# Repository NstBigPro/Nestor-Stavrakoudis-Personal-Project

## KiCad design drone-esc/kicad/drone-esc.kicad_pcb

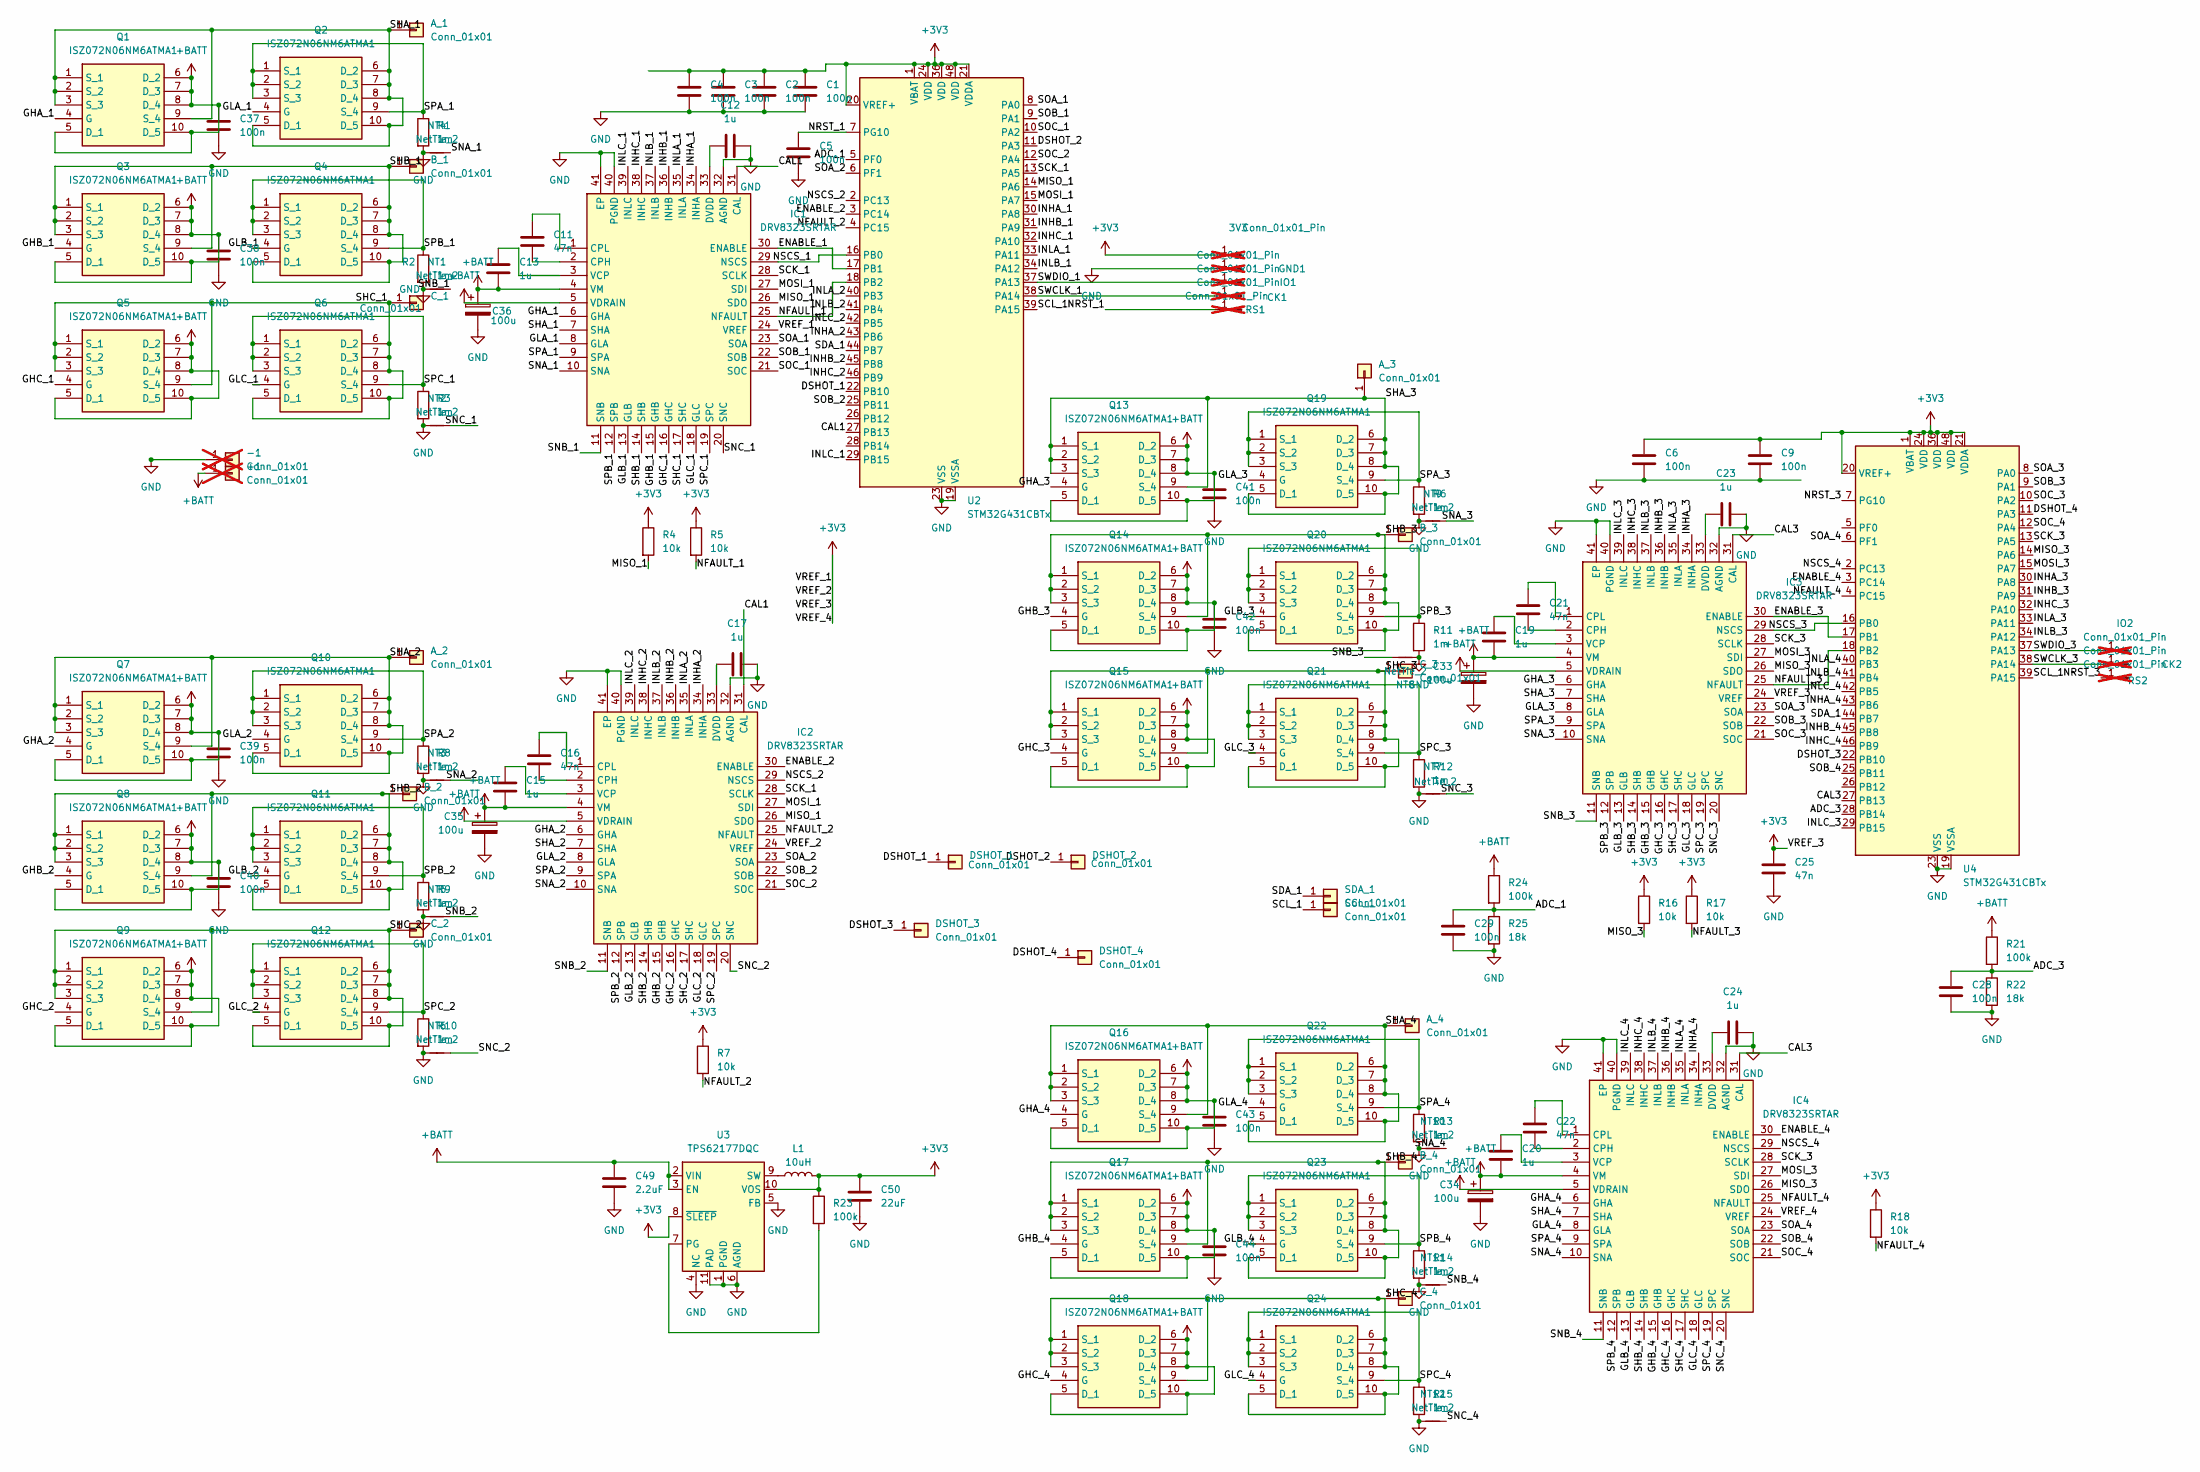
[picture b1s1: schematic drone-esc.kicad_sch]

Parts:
3V3: Conn_01x01_Pin; TestPoint_Pad_D1.0mm; not fitted
+1: Conn_01x01; TestPoint_Loop_D3.80mm_Drill2.5mm; not fitted
-1: Conn_01x01; TestPoint_Loop_D3.80mm_Drill2.5mm; not fitted
A_1, A_2, A_3, A_4: Conn_01x01; SolderWirePad_1x01_SMD_3x6mm
B_1, B_2, B_3, B_4: Conn_01x01; SolderWirePad_1x01_SMD_3x6mm
C1, C2, C3, C4, C5, C6, C9, C28, C29: 100n; C_0402_1005Metric; Mouser Part Number 80-C0402C104K8R7411
C11, C16, C21, C22, C25: 47n; C_0402_1005Metric; Mouser Part Number 81-GRM155R71H473KE4D
C12, C13, C15, C17, C19, C20, C23, C24: 1u; C_0402_1005Metric; Mouser Part Number 346-CM05X5R105M35AH
C33, C34, C35, C36: 100u; CP_Radial_D8.0mm_P3.50mm; Mouser Part Number 667-EEH-AZC1V101B
C37, C38, C39, C40, C41, C42, C43, C44: 100n; C_0805_2012Metric; Mouser Part Number 963-MCASG21GSB5104KT
C49: 2.2uF; C_0805_2012Metric; Mouser Part Number 81-GCJ21BD7YA225KE2L
C50: 22uF; C_0805_2012Metric; Mouser Part Number 963-MLASL21GBB5226MT
CK1, CK2: Conn_01x01_Pin; TestPoint_Pad_D1.0mm; not fitted
C_1, C_2, C_3, C_4: Conn_01x01; SolderWirePad_1x01_SMD_3x6mm
DSHOT_1, DSHOT_2, DSHOT_3, DSHOT_4: Conn_01x01; SolderWirePad_1x01_SMD_3x6mm
GND1: Conn_01x01_Pin; TestPoint_Pad_D1.0mm; not fitted
IC1, IC2, IC3, IC4: DRV8323SRTAR; DRV8323; Manufacturer_Part_Number DRV8323SRTAR; Mouser Part Number 595-DRV8323SRTAT
IO1, IO2: Conn_01x01_Pin; TestPoint_Pad_D1.0mm; not fitted
L1: 10uH; VLS3015; Mouser Part Number 810-VLS3015CX-100M-1
NT1, NT2, NT3, NT4, NT5, NT6, NT7, NT8, NT9, NT10, NT11, NT12: NetTie_2; NetTie-2_SMD_Pad0.5mm
Q1, Q2, Q3, Q4, Q5, Q6, Q7, Q8, Q9, Q10, Q11, Q12, Q13, Q14, Q15, Q16, Q17, Q18, Q19, Q20, Q21, Q22, Q23, Q24: ISZ072N06NM6ATMA1; Manufacturer_Part_Number ISZ072N06NM6ATMA1; Mouser Part Number 726-ISZ072N06NM6ATMA
R1, R2, R3, R6, R8, R9, R10, R11, R12, R13, R14, R15: 1m; R_2512_6332Metric; Mouser Part Number 755-PMR100HZP7FV1L00
R4, R5, R7, R16, R17, R18: 10k; R_0402_1005Metric; Mouser Part Number 603-RT0402FRE0710KL
R21, R23, R24: 100k; R_0402_1005Metric; Mouser Part Number 603-RT0402BRE07100KL
R22, R25: 18k; R_0402_1005Metric; Mouser Part Number 603-AC0402JR-0718KL
RS1, RS2: Conn_01x01_Pin; TestPoint_Pad_D1.0mm; not fitted
SCL_1: Conn_01x01; SolderWirePad_1x01_SMD_2x4mm
SDA_1: Conn_01x01; SolderWirePad_1x01_SMD_2x4mm
U2, U4: STM32G431CBTx; LQFP-48_7x7mm_P0.5mm; Mouser Part Number 511-STM32G431CBT6
U3: TPS62177DQC; WSON-10-1EP_2x3mm_P0.5mm_EP0.84x2.4mm_ThermalVias; Mouser Part Number 595-TPS62177DQCT

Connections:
+3V3: 3V3.1 (Pin_1_1), C1.1, C2.1, C3.1, C4.1, C6.1, C9.1, C25.1, C50.1, IC1.24 (VREF), IC2.24 (VREF), IC3.24 (VREF), IC4.24 (VREF), L1.2, R4.1, R5.1, R7.1, R16.1, R17.1, R18.1, R23.1, U2.1 (VBAT), U2.20 (VREF+), U2.21 (VDDA), U2.24 (VDD), U2.36 (VDD), U2.48 (VDD), U3.8 (~SLEEP), U3.10 (VOS), U4.1 (VBAT), U4.20 (VREF+), U4.21 (VDDA), U4.24 (VDD), U4.36 (VDD), U4.48 (VDD)
+BATT: +1.1 (Pin_1_1), C13.2, C15.2, C19.2, C20.2, C33.1, C34.1, C35.1, C36.1, C37.1, C38.1, C39.1, C40.1, C41.1, C42.1, C43.1, C44.1, C49.1, IC1.4 (VM), IC1.5 (VDRAIN), IC2.4 (VM), IC2.5 (VDRAIN), IC3.4 (VM), IC3.5 (VDRAIN), IC4.4 (VM), IC4.5 (VDRAIN), Q1.5 (D_1), Q1.6 (D_2), Q1.7 (D_3), Q1.8 (D_4), Q1.10 (D_5), Q3.5 (D_1), Q3.6 (D_2), Q3.7 (D_3), Q3.8 (D_4), Q3.10 (D_5), Q5.5 (D_1), Q5.6 (D_2), Q5.7 (D_3), Q5.8 (D_4), Q5.10 (D_5), Q7.5 (D_1), Q7.6 (D_2), Q7.7 (D_3), Q7.8 (D_4), Q7.10 (D_5), Q8.5 (D_1), Q8.6 (D_2), Q8.7 (D_3), Q8.8 (D_4), Q8.10 (D_5), Q9.5 (D_1), Q9.6 (D_2), Q9.7 (D_3), Q9.8 (D_4), Q9.10 (D_5), Q13.5 (D_1), Q13.6 (D_2), Q13.7 (D_3), Q13.8 (D_4), Q13.10 (D_5), Q14.5 (D_1), Q14.6 (D_2), Q14.7 (D_3), Q14.8 (D_4), Q14.10 (D_5), Q15.5 (D_1), Q15.6 (D_2), Q15.7 (D_3), Q15.8 (D_4), Q15.10 (D_5), Q16.5 (D_1), Q16.6 (D_2), Q16.7 (D_3), Q16.8 (D_4), Q16.10 (D_5), Q17.5 (D_1), Q17.6 (D_2), Q17.7 (D_3), Q17.8 (D_4), Q17.10 (D_5), Q18.5 (D_1), Q18.6 (D_2), Q18.7 (D_3), Q18.8 (D_4), Q18.10 (D_5), R21.1, R24.1, U3.2 (VIN), U3.3 (EN)
/ADC_1: C29.1, R24.2, R25.1, U2.5 (PF0)
/ADC_3: C28.1, R21.2, R22.1, U4.28 (PB14)
/CAL1: IC1.31 (CAL), IC2.31 (CAL), U2.27 (PB13)
/CAL3: IC3.31 (CAL), IC4.31 (CAL), U4.27 (PB13)
/DSHOT_1: DSHOT_1.1 (Pin_1_1), U2.22 (PB10)
/DSHOT_2: DSHOT_2.1 (Pin_1_1), U2.11 (PA3)
/DSHOT_3: DSHOT_3.1 (Pin_1_1), U4.22 (PB10)
/DSHOT_4: DSHOT_4.1 (Pin_1_1), U4.11 (PA3)
/ENABLE_1: IC1.30 (ENABLE), U2.17 (PB1)
/ENABLE_2: IC2.30 (ENABLE), U2.3 (PC14)
/ENABLE_3: IC3.30 (ENABLE), U4.17 (PB1)
/ENABLE_4: IC4.30 (ENABLE), U4.3 (PC14)
/GHA_1: IC1.6 (GHA), Q1.4 (G)
/GHA_2: IC2.6 (GHA), Q7.4 (G)
/GHA_3: IC3.6 (GHA), Q13.4 (G)
/GHA_4: IC4.6 (GHA), Q16.4 (G)
/GHB_1: IC1.15 (GHB), Q3.4 (G)
/GHB_2: IC2.15 (GHB), Q8.4 (G)
/GHB_3: IC3.15 (GHB), Q14.4 (G)
/GHB_4: IC4.15 (GHB), Q17.4 (G)
/GHC_1: IC1.16 (GHC), Q5.4 (G)
/GHC_2: IC2.16 (GHC), Q9.4 (G)
/GHC_3: IC3.16 (GHC), Q15.4 (G)
/GHC_4: IC4.16 (GHC), Q18.4 (G)
/GLA_1: IC1.8 (GLA), Q2.4 (G)
/GLA_2: IC2.8 (GLA), Q10.4 (G)
/GLA_3: IC3.8 (GLA), Q19.4 (G)
/GLA_4: IC4.8 (GLA), Q22.4 (G)
/GLB_1: IC1.13 (GLB), Q4.4 (G)
/GLB_2: IC2.13 (GLB), Q11.4 (G)
/GLB_3: IC3.13 (GLB), Q20.4 (G)
/GLB_4: IC4.13 (GLB), Q23.4 (G)
/GLC_1: IC1.18 (GLC), Q6.4 (G)
/GLC_2: IC2.18 (GLC), Q12.4 (G)
/GLC_3: IC3.18 (GLC), Q21.4 (G)
/GLC_4: IC4.18 (GLC), Q24.4 (G)
/INHA_1: IC1.34 (INHA), U2.30 (PA8)
/INHA_2: IC2.34 (INHA), U2.43 (PB6)
/INHA_3: IC3.34 (INHA), U4.30 (PA8)
/INHA_4: IC4.34 (INHA), U4.43 (PB6)
/INHB_1: IC1.36 (INHB), U2.31 (PA9)
/INHB_2: IC2.36 (INHB), U2.45 (PB8)
/INHB_3: IC3.36 (INHB), U4.31 (PA9)
/INHB_4: IC4.36 (INHB), U4.45 (PB8)
/INHC_1: IC1.38 (INHC), U2.32 (PA10)
/INHC_2: IC2.38 (INHC), U2.46 (PB9)
/INHC_3: IC3.38 (INHC), U4.32 (PA10)
/INHC_4: IC4.38 (INHC), U4.46 (PB9)
/INLA_1: IC1.35 (INLA), U2.33 (PA11)
/INLA_2: IC2.35 (INLA), U2.40 (PB3)
/INLA_3: IC3.35 (INLA), U4.33 (PA11)
/INLA_4: IC4.35 (INLA), U4.40 (PB3)
/INLB_1: IC1.37 (INLB), U2.34 (PA12)
/INLB_2: IC2.37 (INLB), U2.41 (PB4)
/INLB_3: IC3.37 (INLB), U4.34 (PA12)
/INLB_4: IC4.37 (INLB), U4.41 (PB4)
/INLC_1: IC1.39 (INLC), U2.29 (PB15)
/INLC_2: IC2.39 (INLC), U2.42 (PB5)
/INLC_3: IC3.39 (INLC), U4.29 (PB15)
/INLC_4: IC4.39 (INLC), U4.42 (PB5)
/MISO_1: IC1.26 (SDO), IC2.26 (SDO), R4.2, U2.14 (PA6)
/MISO_3: IC3.26 (SDO), IC4.26 (SDO), R16.2, U4.14 (PA6)
/MOSI_1: IC1.27 (SDI), IC2.27 (SDI), U2.15 (PA7)
/MOSI_3: IC3.27 (SDI), IC4.27 (SDI), U4.15 (PA7)
/NFAULT_1: IC1.25 (NFAULT), R5.2, U2.18 (PB2)
/NFAULT_2: IC2.25 (NFAULT), R7.2, U2.4 (PC15)
/NFAULT_3: IC3.25 (NFAULT), R17.2, U4.18 (PB2)
/NFAULT_4: IC4.25 (NFAULT), R18.2, U4.4 (PC15)
/NRST_1: C5.1, RS1.1 (Pin_1_1), U2.7 (PG10)
/NRST_3: RS2.1 (Pin_1_1), U4.7 (PG10)
/NSCS_1: IC1.29 (NSCS), U2.16 (PB0)
/NSCS_2: IC2.29 (NSCS), U2.2 (PC13)
/NSCS_3: IC3.29 (NSCS), U4.16 (PB0)
/NSCS_4: IC4.29 (NSCS), U4.2 (PC13)
/SCK_1: IC1.28 (SCLK), IC2.28 (SCLK), U2.13 (PA5)
/SCK_3: IC3.28 (SCLK), IC4.28 (SCLK), U4.13 (PA5)
/SCL_1: SCL_1.1 (Pin_1_1), U2.39 (PA15), U4.39 (PA15)
/SDA_1: SDA_1.1 (Pin_1_1), U2.44 (PB7), U4.44 (PB7)
/SHA_1: A_1.1 (Pin_1_1), IC1.7 (SHA), Q1.1 (S_1), Q1.2 (S_2), Q1.3 (S_3), Q1.9 (S_4), Q2.5 (D_1), Q2.6 (D_2), Q2.7 (D_3), Q2.8 (D_4), Q2.10 (D_5)
/SHA_2: A_2.1 (Pin_1_1), IC2.7 (SHA), Q7.1 (S_1), Q7.2 (S_2), Q7.3 (S_3), Q7.9 (S_4), Q10.5 (D_1), Q10.6 (D_2), Q10.7 (D_3), Q10.8 (D_4), Q10.10 (D_5)
/SHA_3: A_3.1 (Pin_1_1), IC3.7 (SHA), Q13.1 (S_1), Q13.2 (S_2), Q13.3 (S_3), Q13.9 (S_4), Q19.5 (D_1), Q19.6 (D_2), Q19.7 (D_3), Q19.8 (D_4), Q19.10 (D_5)
/SHA_4: A_4.1 (Pin_1_1), IC4.7 (SHA), Q16.1 (S_1), Q16.2 (S_2), Q16.3 (S_3), Q16.9 (S_4), Q22.5 (D_1), Q22.6 (D_2), Q22.7 (D_3), Q22.8 (D_4), Q22.10 (D_5)
/SHB_1: B_1.1 (Pin_1_1), IC1.14 (SHB), Q3.1 (S_1), Q3.2 (S_2), Q3.3 (S_3), Q3.9 (S_4), Q4.5 (D_1), Q4.6 (D_2), Q4.7 (D_3), Q4.8 (D_4), Q4.10 (D_5)
/SHB_2: B_2.1 (Pin_1_1), IC2.14 (SHB), Q8.1 (S_1), Q8.2 (S_2), Q8.3 (S_3), Q8.9 (S_4), Q11.5 (D_1), Q11.6 (D_2), Q11.7 (D_3), Q11.8 (D_4), Q11.10 (D_5)
/SHB_3: B_3.1 (Pin_1_1), IC3.14 (SHB), Q14.1 (S_1), Q14.2 (S_2), Q14.3 (S_3), Q14.9 (S_4), Q20.5 (D_1), Q20.6 (D_2), Q20.7 (D_3), Q20.8 (D_4), Q20.10 (D_5)
/SHB_4: B_4.1 (Pin_1_1), IC4.14 (SHB), Q17.1 (S_1), Q17.2 (S_2), Q17.3 (S_3), Q17.9 (S_4), Q23.5 (D_1), Q23.6 (D_2), Q23.7 (D_3), Q23.8 (D_4), Q23.10 (D_5)
/SHC_1: C_1.1 (Pin_1_1), IC1.17 (SHC), Q5.1 (S_1), Q5.2 (S_2), Q5.3 (S_3), Q5.9 (S_4), Q6.5 (D_1), Q6.6 (D_2), Q6.7 (D_3), Q6.8 (D_4), Q6.10 (D_5)
/SHC_2: C_2.1 (Pin_1_1), IC2.17 (SHC), Q9.1 (S_1), Q9.2 (S_2), Q9.3 (S_3), Q9.9 (S_4), Q12.5 (D_1), Q12.6 (D_2), Q12.7 (D_3), Q12.8 (D_4), Q12.10 (D_5)
/SHC_3: C_3.1 (Pin_1_1), IC3.17 (SHC), Q15.1 (S_1), Q15.2 (S_2), Q15.3 (S_3), Q15.9 (S_4), Q21.5 (D_1), Q21.6 (D_2), Q21.7 (D_3), Q21.8 (D_4), Q21.10 (D_5)
/SHC_4: C_4.1 (Pin_1_1), IC4.17 (SHC), Q18.1 (S_1), Q18.2 (S_2), Q18.3 (S_3), Q18.9 (S_4), Q24.5 (D_1), Q24.6 (D_2), Q24.7 (D_3), Q24.8 (D_4), Q24.10 (D_5)
/SNA_1: IC1.10 (SNA), NT4.1
/SNA_2: IC2.10 (SNA), NT3.2
/SNA_3: IC3.10 (SNA), NT9.2
/SNA_4: IC4.10 (SNA), NT10.2
/SNB_1: IC1.11 (SNB), NT1.2
/SNB_2: IC2.11 (SNB), NT5.2
/SNB_3: IC3.11 (SNB), NT8.2
/SNB_4: IC4.11 (SNB), NT11.2
/SNC_1: IC1.20 (SNC), NT2.2
/SNC_2: IC2.20 (SNC), NT6.2
/SNC_3: IC3.20 (SNC), NT7.2
/SNC_4: IC4.20 (SNC), NT12.2
/SOA_1: IC1.23 (SOA), U2.8 (PA0)
/SOA_2: IC2.23 (SOA), U2.6 (PF1)
/SOA_3: IC3.23 (SOA), U4.8 (PA0)
/SOA_4: IC4.23 (SOA), U4.6 (PF1)
/SOB_1: IC1.22 (SOB), U2.9 (PA1)
/SOB_2: IC2.22 (SOB), U2.25 (PB11)
/SOB_3: IC3.22 (SOB), U4.9 (PA1)
/SOB_4: IC4.22 (SOB), U4.25 (PB11)
/SOC_1: IC1.21 (SOC), U2.10 (PA2)
/SOC_2: IC2.21 (SOC), U2.12 (PA4)
/SOC_3: IC3.21 (SOC), U4.10 (PA2)
/SOC_4: IC4.21 (SOC), U4.12 (PA4)
/SPA_1: IC1.9 (SPA), Q2.1 (S_1), Q2.2 (S_2), Q2.3 (S_3), Q2.9 (S_4), R1.1
/SPA_2: IC2.9 (SPA), Q10.1 (S_1), Q10.2 (S_2), Q10.3 (S_3), Q10.9 (S_4), R8.1
/SPA_3: IC3.9 (SPA), Q19.1 (S_1), Q19.2 (S_2), Q19.3 (S_3), Q19.9 (S_4), R6.1
/SPA_4: IC4.9 (SPA), Q22.1 (S_1), Q22.2 (S_2), Q22.3 (S_3), Q22.9 (S_4), R13.1
/SPB_1: IC1.12 (SPB), Q4.1 (S_1), Q4.2 (S_2), Q4.3 (S_3), Q4.9 (S_4), R2.1
/SPB_2: IC2.12 (SPB), Q11.1 (S_1), Q11.2 (S_2), Q11.3 (S_3), Q11.9 (S_4), R9.1
/SPB_3: IC3.12 (SPB), Q20.1 (S_1), Q20.2 (S_2), Q20.3 (S_3), Q20.9 (S_4), R11.1
/SPB_4: IC4.12 (SPB), Q23.1 (S_1), Q23.2 (S_2), Q23.3 (S_3), Q23.9 (S_4), R14.1
/SPC_1: IC1.19 (SPC), Q6.1 (S_1), Q6.2 (S_2), Q6.3 (S_3), Q6.9 (S_4), R3.1
/SPC_2: IC2.19 (SPC), Q12.1 (S_1), Q12.2 (S_2), Q12.3 (S_3), Q12.9 (S_4), R10.1
/SPC_3: IC3.19 (SPC), Q21.1 (S_1), Q21.2 (S_2), Q21.3 (S_3), Q21.9 (S_4), R12.1
/SPC_4: IC4.19 (SPC), Q24.1 (S_1), Q24.2 (S_2), Q24.3 (S_3), Q24.9 (S_4), R15.1
/SWCLK_1: CK1.1 (Pin_1_1), U2.38 (PA14)
/SWCLK_3: CK2.1 (Pin_1_1), U4.38 (PA14)
/SWDIO_1: IO1.1 (Pin_1_1), U2.37 (PA13)
/SWDIO_3: IO2.1 (Pin_1_1), U4.37 (PA13)
GND: -1.1 (Pin_1_1), C1.2, C2.2, C3.2, C4.2, C5.2, C6.2, C9.2, C12.2, C17.2, C23.2, C24.2, C25.2, C28.2, C29.2, C33.2, C34.2, C35.2, C36.2, C37.2, C38.2, C39.2, C40.2, C41.2, C42.2, C43.2, C44.2, C49.2, C50.2, GND1.1 (Pin_1_1), IC1.32 (AGND), IC1.40 (PGND), IC1.41 (EP), IC2.32 (AGND), IC2.40 (PGND), IC2.41 (EP), IC3.32 (AGND), IC3.40 (PGND), IC3.41 (EP), IC4.32 (AGND), IC4.40 (PGND), IC4.41 (EP), NT1.1, NT2.1, NT3.1, NT4.2, NT5.1, NT6.1, NT7.1, NT8.1, NT9.1, NT10.1, NT11.1, NT12.1, R1.2, R2.2, R3.2, R6.2, R8.2, R9.2, R10.2, R11.2, R12.2, R13.2, R14.2, R15.2, R22.2, R25.2, U2.19 (VSSA), U2.23 (VSS), U2.35 (VSS), U2.47 (VSS), U3.1 (PGND), U3.4 (NC), U3.5 (FB), U3.6 (AGND), U3.11 (PAD), U4.19 (VSSA), U4.23 (VSS), U4.35 (VSS), U4.47 (VSS)
unnamed: C11.2, IC1.2 (CPH)
unnamed: C11.1, IC1.1 (CPL)
unnamed: C12.1, IC1.33 (DVDD)
unnamed: C13.1, IC1.3 (VCP)
unnamed: C16.2, IC2.2 (CPH)
unnamed: C16.1, IC2.1 (CPL)
unnamed: C17.1, IC2.33 (DVDD)
unnamed: C15.1, IC2.3 (VCP)
unnamed: C21.2, IC3.2 (CPH)
unnamed: C21.1, IC3.1 (CPL)
unnamed: C23.1, IC3.33 (DVDD)
unnamed: C19.1, IC3.3 (VCP)
unnamed: C22.2, IC4.2 (CPH)
unnamed: C22.1, IC4.1 (CPL)
unnamed: C24.1, IC4.33 (DVDD)
unnamed: C20.1, IC4.3 (VCP)
unnamed: R23.2, U3.7 (PG)
unnamed: L1.1, U3.9 (SW)

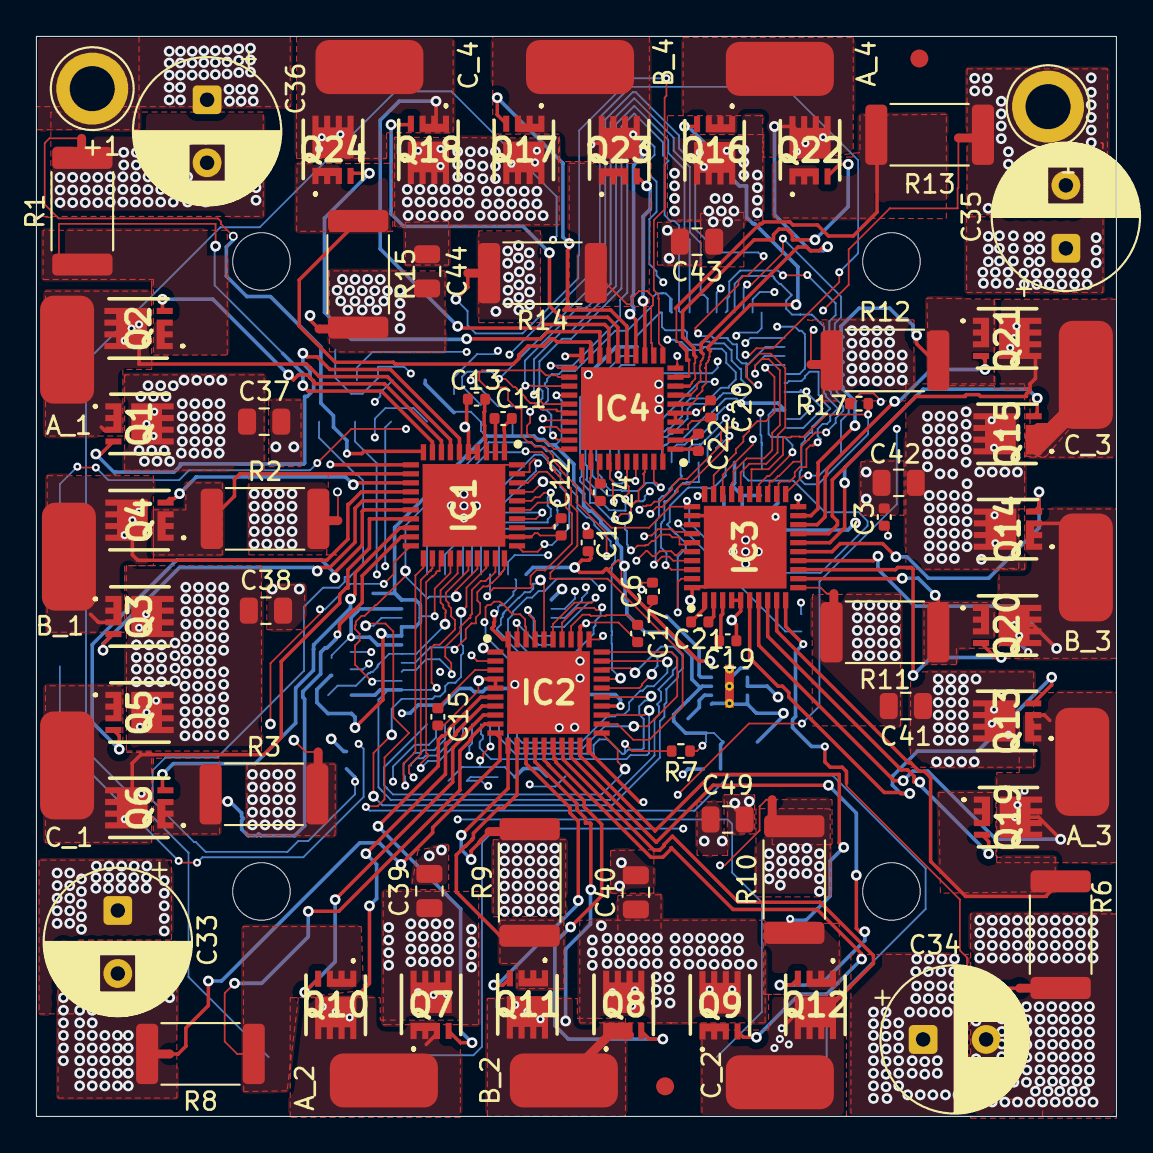
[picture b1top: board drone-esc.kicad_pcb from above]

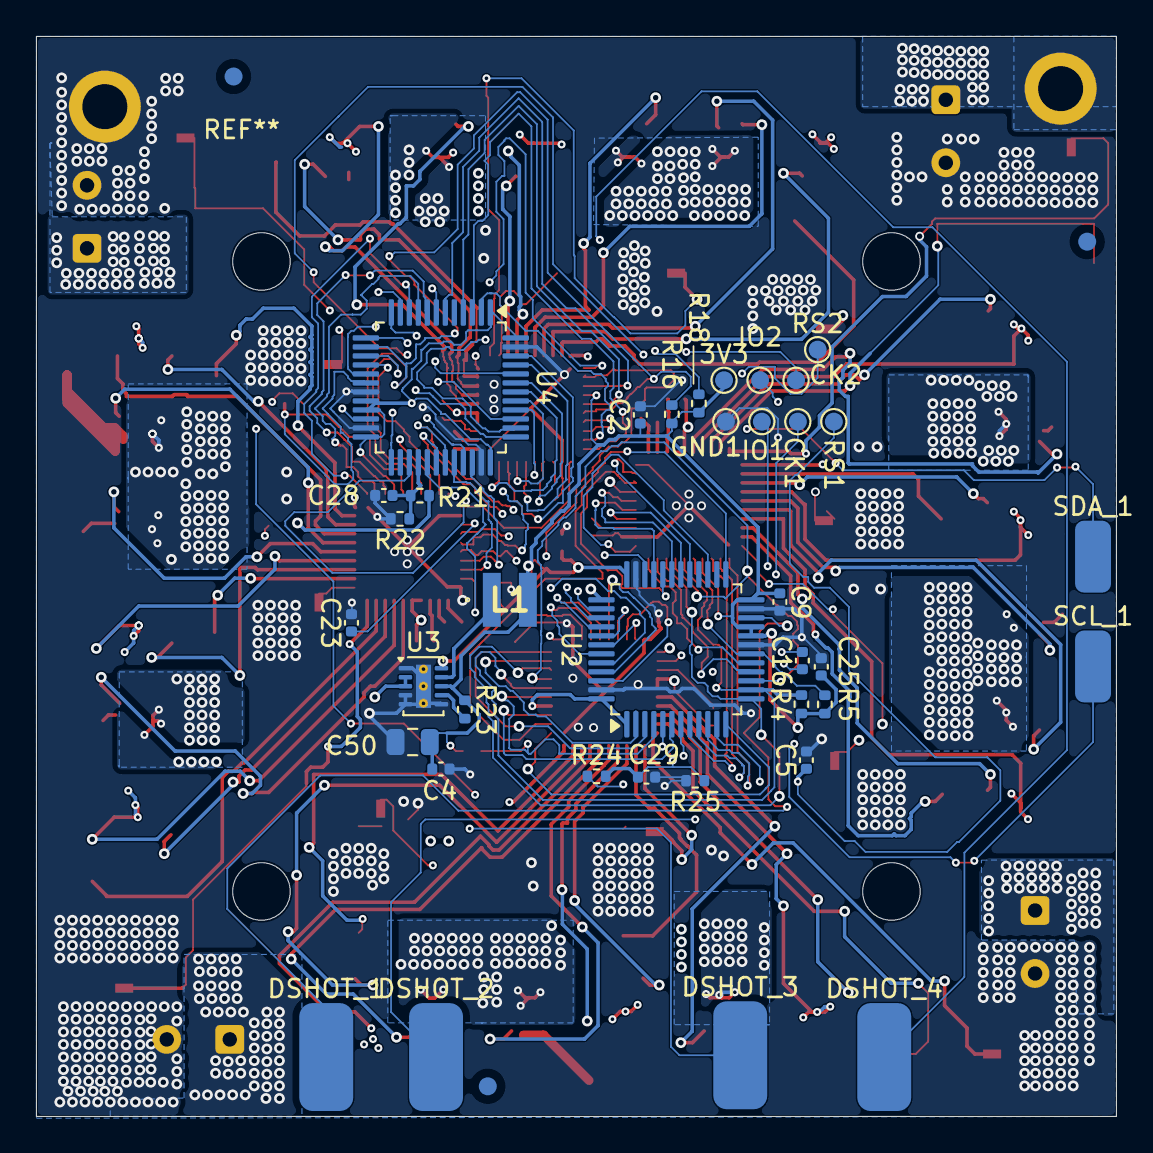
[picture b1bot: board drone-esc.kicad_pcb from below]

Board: 4 copper layers, 60.0 x 60.0 mm, 131 parts (37 on the bottom side), 151 nets.

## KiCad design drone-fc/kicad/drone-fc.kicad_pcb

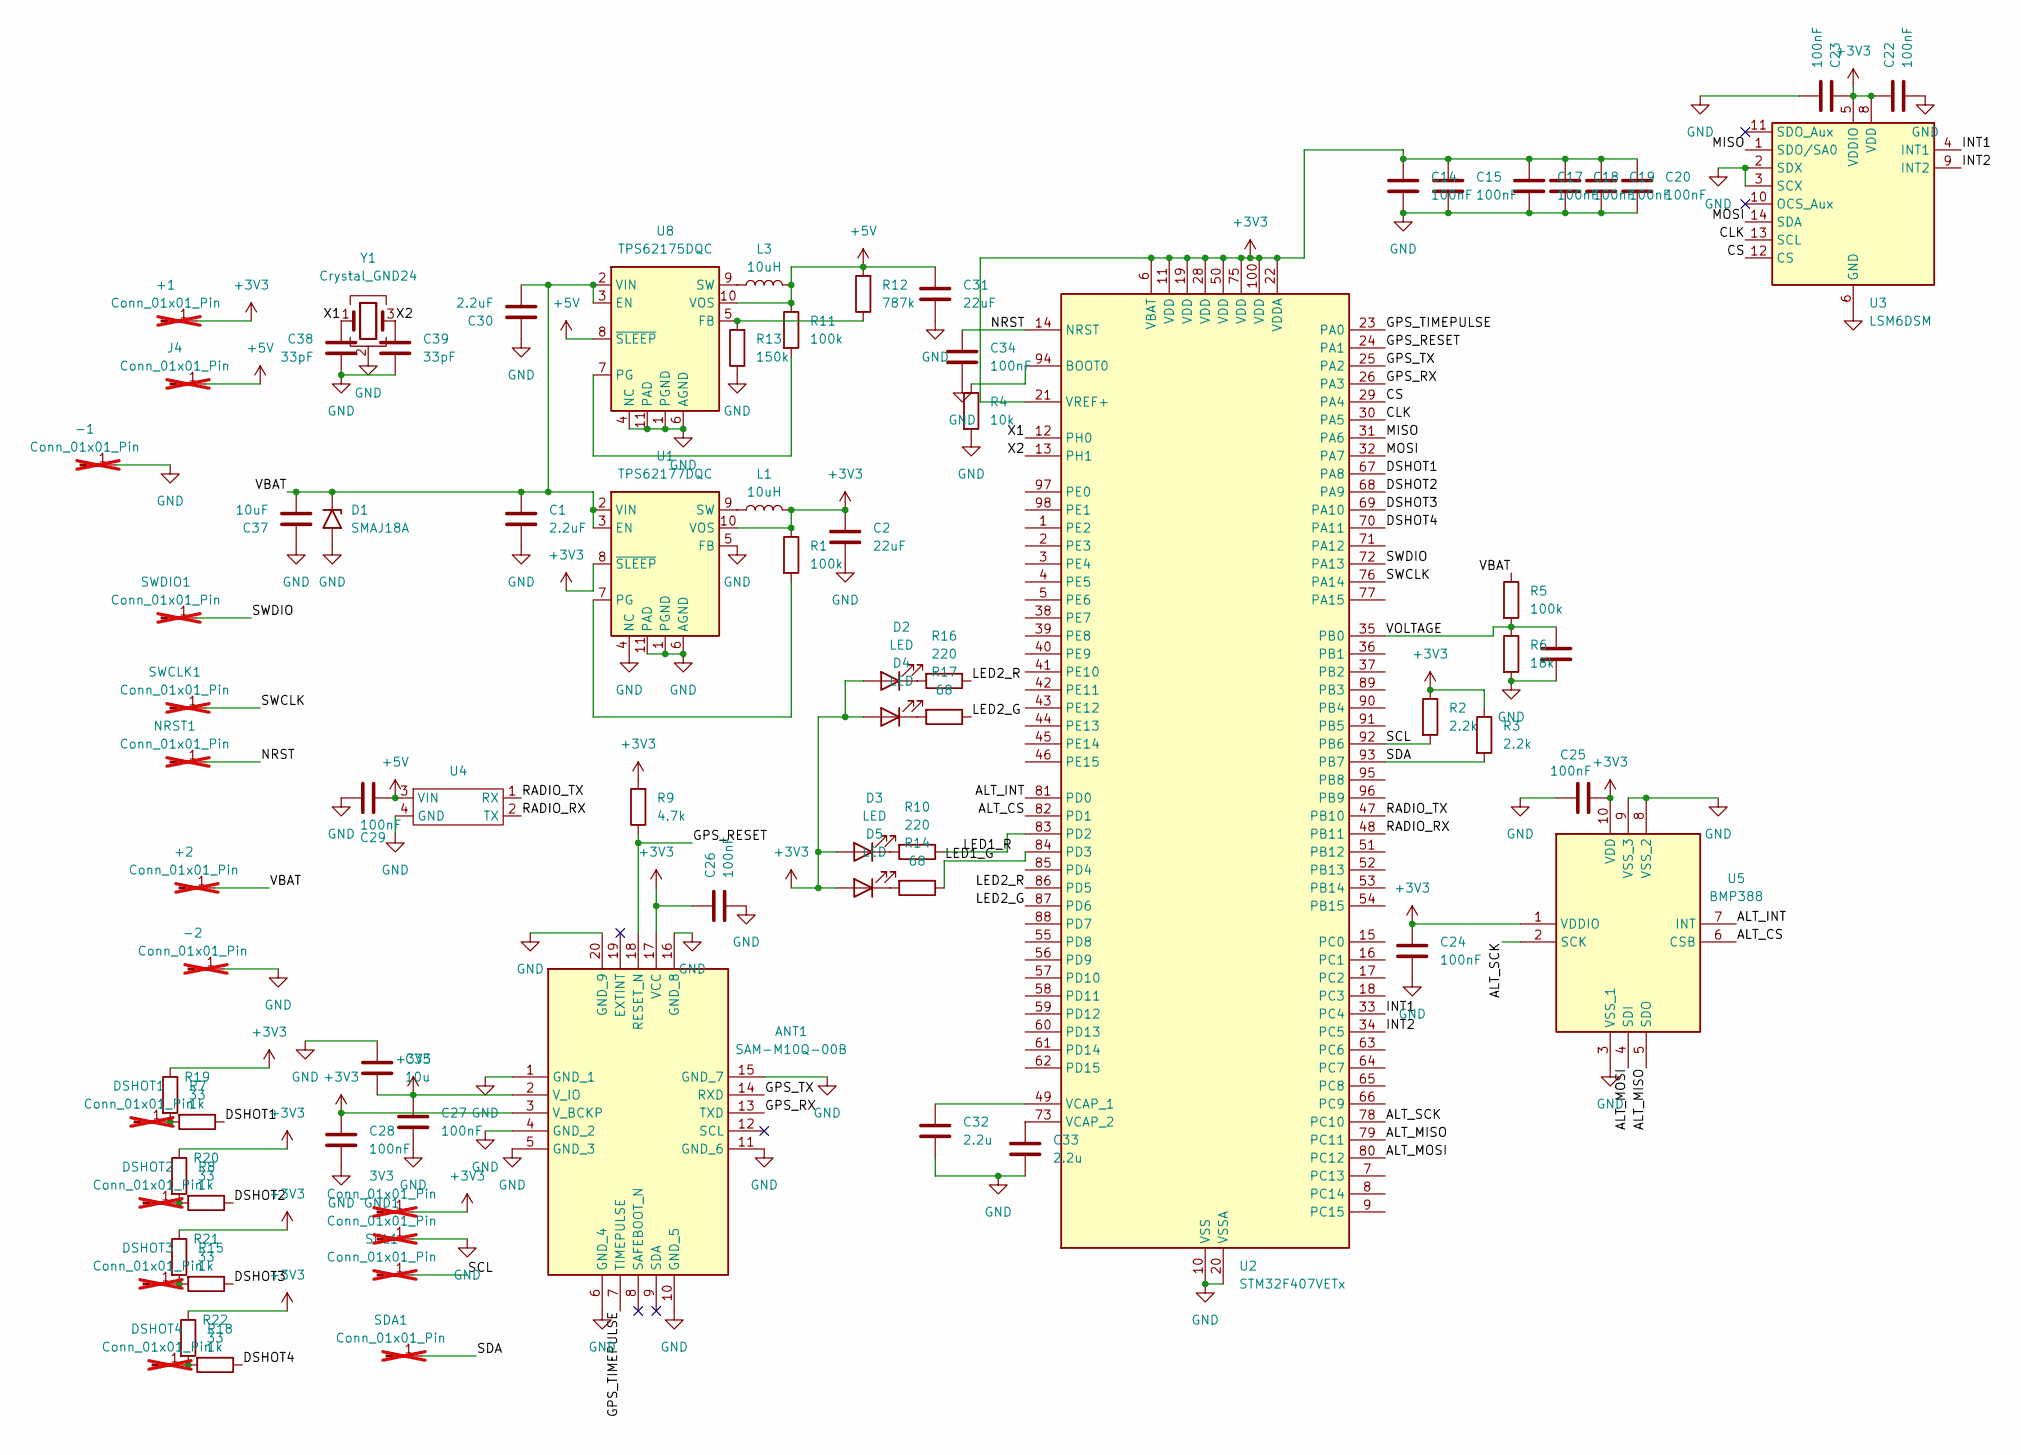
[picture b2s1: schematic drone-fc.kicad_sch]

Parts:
3V3: Conn_01x01_Pin; SolderWirePad_1x01_SMD_1.5x3mm; not fitted
+1: Conn_01x01_Pin; TestPoint_Pad_D1.0mm; not fitted
+2: Conn_01x01_Pin; SolderWirePad_1x01_SMD_2x4mm; not fitted
-1: Conn_01x01_Pin; TestPoint_Pad_D1.0mm; not fitted
-2: Conn_01x01_Pin; SolderWirePad_1x01_SMD_2x4mm; not fitted
ANT1: SAM-M10Q-00B; SAMM10Q00B; Manufacturer_Part_Number SAM-M10Q-00B; Mouser Part Number 377-SAM-M10Q-00B
C1, C30: 2.2uF; C_0805_2012Metric; Mouser Part Number 187-CL21A225KB9LNNC
C2, C31: 22uF; C_0805_2012Metric; Mouser Part Number 963-MLASL21GBB5226MT
C14, C15, C17, C18, C19, C20, C22, C23, C24, C25, C26, C27, C28, C29, C34, C36: 100nF; C_0402_1005Metric; Mouser Part Number 80-C0402C104K8R7411
C32, C33: 2.2u; C_0603_1608Metric; Mouser Part Number 81-GRM188R71A225KE5J
C35: 10u; C_0805_2012Metric; Mouser Part Number 80-C0805C106K3P
C37: 10uF; C_0805_2012Metric; Mouser Part Number 810-C2012X5R1V106K0C
C38, C39: 33pF; C_0402_1005Metric; Mouser Part Number 710-885012005043
D1: SMAJ18A; D_SMA; Mouser Part Number 576-SMAJ18A
D2, D3: LED; LED_0603_1608Metric; Mouser Part Number 710-150060RS75000
D4, D5: LED; LED_0603_1608Metric; Mouser Part Number 710-150060VS75000
DSHOT1, DSHOT2, DSHOT3, DSHOT4: Conn_01x01_Pin; SolderWirePad_1x01_SMD_1.5x3mm; not fitted
GND1: Conn_01x01_Pin; SolderWirePad_1x01_SMD_1.5x3mm; not fitted
J4: Conn_01x01_Pin; TestPoint_Pad_D1.0mm; not fitted
L1, L3: 10uH; VLS3015; Mouser Part Number 810-VLS3015CX-100M-1
NRST1: Conn_01x01_Pin; TestPoint_Pad_D1.0mm; not fitted
R1, R5, R11: 100k; R_0402_1005Metric; Mouser Part Number 603-RT0402BRE07100KL
R2, R3: 2.2k; R_0402_1005Metric; Mouser Part Number 603-RC0402JR-072K2L
R4: 10k; R_0402_1005Metric; Mouser Part Number 603-RT0402FRE0710KL
R6: 18k; R_0402_1005Metric; Mouser Part Number 603-RC0402BR-0718KL
R7, R8, R15, R18: 1k; R_0402_1005Metric; Mouser Part Number 71-RCA04021K00FKEDSR
R9: 4.7k; R_0402_1005Metric; Mouser Part Number 603-RC0402FR-134K7L
R10, R16: 220; R_0402_1005Metric; Mouser Part Number 71-RCS0402220RJNED
R12: 787k; R_0402_1005Metric; Mouser Part Number 603-RC0402FR-07787KL
R13: 150k; R_0402_1005Metric; Mouser Part Number 603-AF0402FR-07150KL
R14, R17: 68; R_0402_1005Metric; Mouser Part Number 71-RCS040268R0FKED
R19, R20, R21, R22: 33; R_0402_1005Metric; Mouser Part Number 71-CRCW0402-33-E3
SCL1: Conn_01x01_Pin; SolderWirePad_1x01_SMD_1.5x3mm; not fitted
SDA1: Conn_01x01_Pin; SolderWirePad_1x01_SMD_1.5x3mm; not fitted
SWCLK1: Conn_01x01_Pin; TestPoint_Pad_D1.0mm; not fitted
SWDIO1: Conn_01x01_Pin; TestPoint_Pad_D1.0mm; not fitted
U1: TPS62177DQC; WSON-10-1EP_2x3mm_P0.5mm_EP0.84x2.4mm_ThermalVias; Mouser Part Number 595-TPS62177DQCT
U2: STM32F407VETx; LQFP-100_14x14mm_P0.5mm; Mouser Part Number 511-STM32F407VET6
U3: LSM6DSM; LGA-14_3x2.5mm_P0.5mm_LayoutBorder3x4y; Mouser Part Number 511-LSM6DSV32XTR
U4: EP1
U5: BMP388; Manufacturer_Part_Number BMP581; Mouser Part Number 262-BMP581
U8: TPS62175DQC; WSON-10-1EP_2x3mm_P0.5mm_EP0.84x2.4mm_ThermalVias; Mouser Part Number 595-TPS62175DQCR
Y1: Crystal_GND24; Crystal_SMD_Abracon_ABM3B-4Pin_5.0x3.2mm; Mouser Part Number 815-AM3N2400018D2YT

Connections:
+3V3: 3V3.1 (Pin_1_1), +1.1 (Pin_1_1), ANT1.2 (V_IO), ANT1.3 (V_BCKP), ANT1.17 (VCC), C2.1, C14.1, C15.1, C17.1, C18.1, C19.1, C20.1, C22.1, C23.1, C24.1, C25.2, C26.1, C27.1, C28.1, C35.2, D2.2 (A), D3.2 (A), D4.2 (A), D5.2 (A), L1.2, R1.1, R2.1, R3.1, R7.1, R8.1, R9.2, R15.1, R18.1, U1.8 (~SLEEP), U1.10 (VOS), U2.6 (VBAT), U2.11 (VDD), U2.19 (VDD), U2.21 (VREF+), U2.22 (VDDA), U2.28 (VDD), U2.50 (VDD), U2.75 (VDD), U2.100 (VDD), U3.5 (VDDIO), U3.8 (VDD), U5.1 (VDDIO), U5.10 (VDD)
+5V: C29.1, C31.1, J4.1 (Pin_1_1), L3.2, R11.1, R12.2, U4.3 (VIN), U8.8 (~SLEEP), U8.10 (VOS)
/ALT_CS: U2.82 (PD1), U5.6 (CSB)
/ALT_INT: U2.81 (PD0), U5.7 (INT)
/ALT_MISO: U2.79 (PC11), U5.5 (SDO)
/ALT_MOSI: U2.80 (PC12), U5.4 (SDI)
/ALT_SCK: U2.78 (PC10), U5.2 (SCK)
/CLK: U2.30 (PA5), U3.13 (SCL)
/CS: U2.29 (PA4), U3.12 (CS)
/DSHOT1: R19.1, U2.67 (PA8)
/DSHOT2: R20.1, U2.68 (PA9)
/DSHOT3: R21.1, U2.69 (PA10)
/DSHOT4: R22.1, U2.70 (PA11)
/GPS_RESET: ANT1.18 (RESET_N), R9.1, U2.24 (PA1)
/GPS_RX: ANT1.13 (TXD), U2.26 (PA3)
/GPS_TIMEPULSE: ANT1.7 (TIMEPULSE), U2.23 (PA0)
/GPS_TX: ANT1.14 (RXD), U2.25 (PA2)
/INT1: U2.33 (PC4), U3.4 (INT1)
/INT2: U2.34 (PC5), U3.9 (INT2)
/LED1_G: R14.1, U2.84 (PD3)
/LED1_R: R10.1, U2.83 (PD2)
/LED2_G: R17.1, U2.87 (PD6)
/LED2_R: R16.1, U2.86 (PD5)
/MISO: U2.31 (PA6), U3.1 (SDO/SA0)
/MOSI: U2.32 (PA7), U3.14 (SDA)
/NRST: C34.1, NRST1.1 (Pin_1_1), U2.14 (NRST)
/RADIO_RX: U2.48 (PB11), U4.2 (TX)
/RADIO_TX: U2.47 (PB10), U4.1 (RX)
/SCL: R2.2, SCL1.1 (Pin_1_1), U2.92 (PB6)
/SDA: R3.2, SDA1.1 (Pin_1_1), U2.93 (PB7)
/SWCLK: SWCLK1.1 (Pin_1_1), U2.76 (PA14)
/SWDIO: SWDIO1.1 (Pin_1_1), U2.72 (PA13)
/VBAT: +2.1 (Pin_1_1), C1.1, C30.2, C37.2, D1.1 (A1), R5.1, U1.2 (VIN), U1.3 (EN), U8.2 (VIN), U8.3 (EN)
/VOLTAGE: C36.1, R5.2, R6.1, U2.35 (PB0)
/X1: C38.1, U2.12 (PH0), Y1.1
/X2: C39.1, U2.13 (PH1), Y1.3
GND: -1.1 (Pin_1_1), -2.1 (Pin_1_1), ANT1.1 (GND_1), ANT1.4 (GND_2), ANT1.5 (GND_3), ANT1.6 (GND_4), ANT1.10 (GND_5), ANT1.11 (GND_6), ANT1.15 (GND_7), ANT1.16 (GND_8), ANT1.20 (GND_9), C1.2, C2.2, C14.2, C15.2, C17.2, C18.2, C19.2, C20.2, C22.2, C23.2, C24.2, C25.1, C26.2, C27.2, C28.2, C29.2, C30.1, C31.2, C32.2, C33.2, C34.2, C35.1, C36.2, C37.1, C38.2, C39.2, D1.2 (A2), GND1.1 (Pin_1_1), R4.2, R6.2, R13.1, U1.1 (PGND), U1.4 (NC), U1.5 (FB), U1.6 (AGND), U1.11 (PAD), U2.10 (VSS), U2.20 (VSSA), U2.27 (VSS), U2.74 (VSS), U2.99 (VSS), U3.2 (SDX), U3.3 (SCX), U3.6 (GND), U3.7 (GND), U4.4 (GND), U5.3 (VSS_1), U5.8 (VSS_2), U5.9 (VSS_3), U8.1 (PGND), U8.4 (NC), U8.6 (AGND), U8.11 (PAD), Y1.2 (G), Y1.4 (G)
unnamed: D2.1 (K), R16.2
unnamed: D3.1 (K), R10.2
unnamed: D4.1 (K), R17.2
unnamed: D5.1 (K), R14.2
unnamed: DSHOT1.1 (Pin_1_1), R7.2, R19.2
unnamed: DSHOT2.1 (Pin_1_1), R8.2, R20.2
unnamed: DSHOT3.1 (Pin_1_1), R15.2, R21.2
unnamed: DSHOT4.1 (Pin_1_1), R18.2, R22.2
unnamed: R1.2, U1.7 (PG)
unnamed: L1.1, U1.9 (SW)
unnamed: R4.1, U2.94 (BOOT0)
unnamed: C32.1, U2.49 (VCAP_1)
unnamed: C33.1, U2.73 (VCAP_2)
unnamed: R12.1, R13.2, U8.5 (FB)
unnamed: R11.2, U8.7 (PG)
unnamed: L3.1, U8.9 (SW)

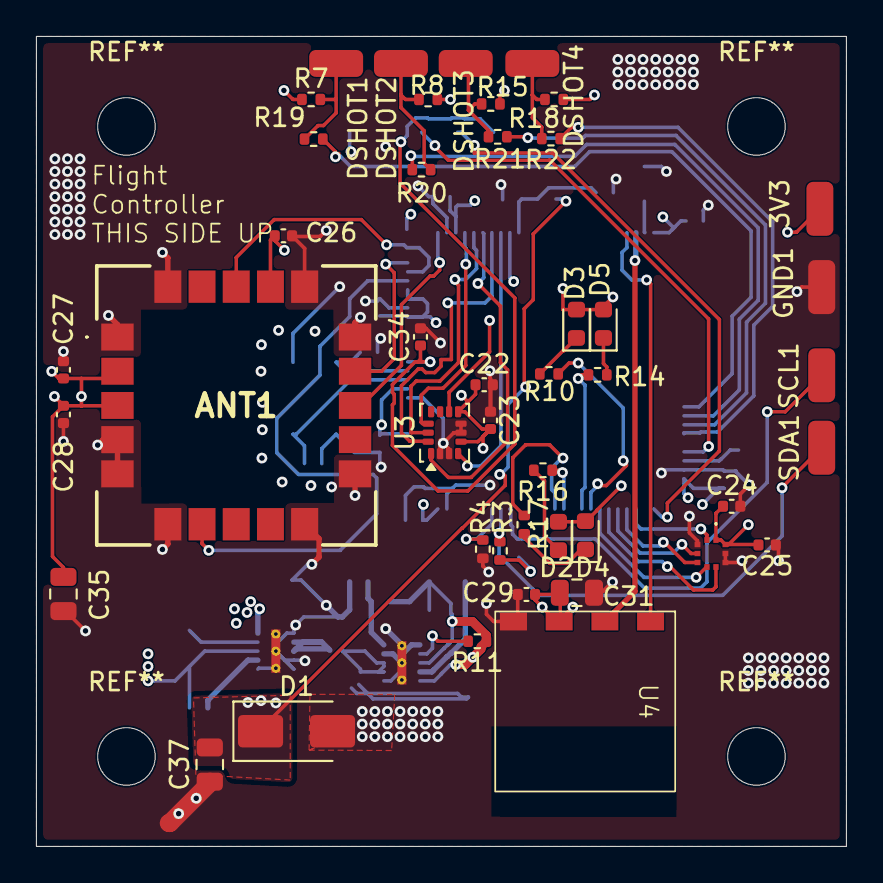
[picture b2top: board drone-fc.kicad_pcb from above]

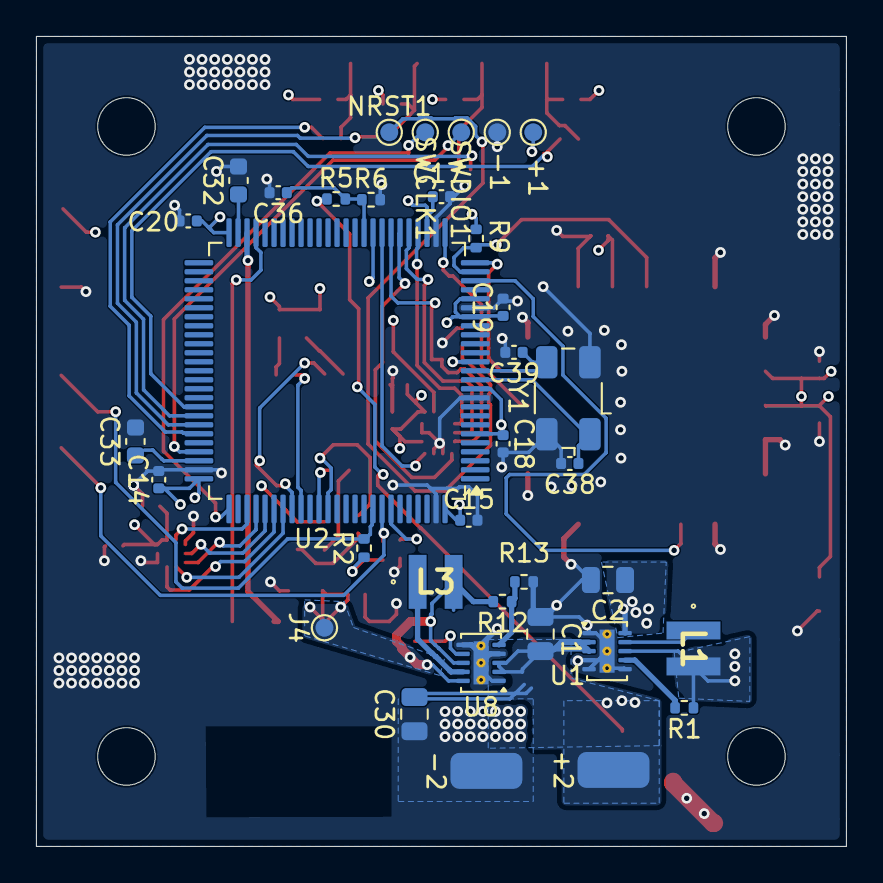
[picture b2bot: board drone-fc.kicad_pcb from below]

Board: 4 copper layers, 45.0 x 45.0 mm, 79 parts (35 on the bottom side), 53 nets.
